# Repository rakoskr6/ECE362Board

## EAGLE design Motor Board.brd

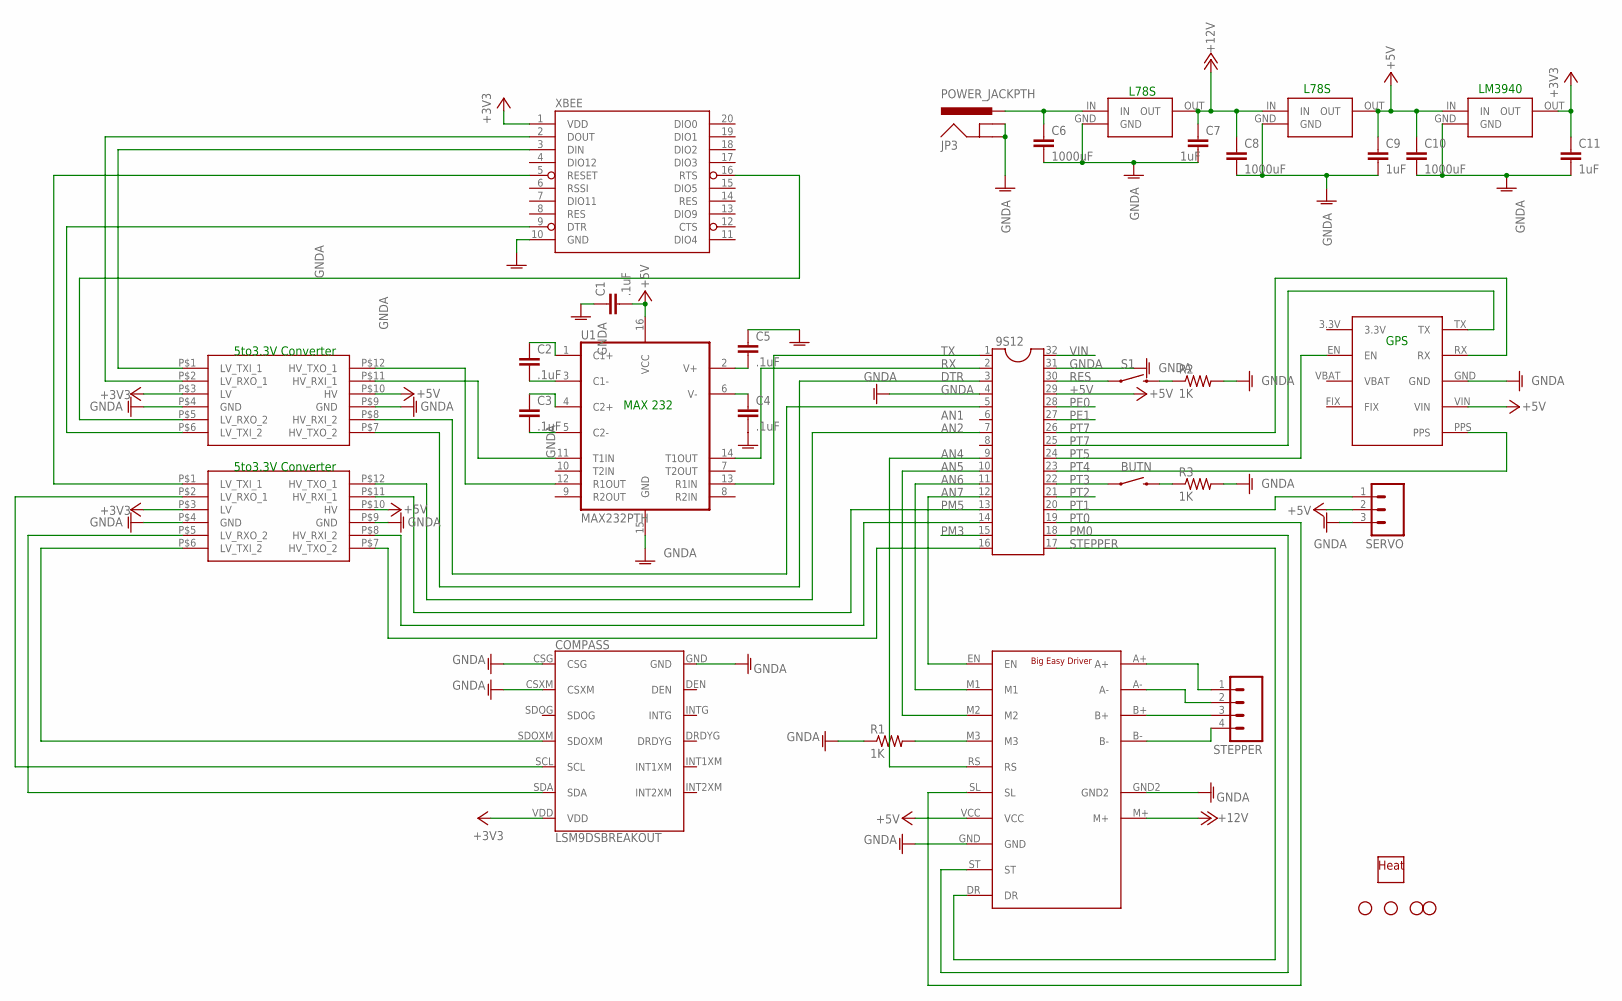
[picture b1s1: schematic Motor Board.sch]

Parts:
9S12: DIL32
BUTN: EXTERNALBUTTON
C1, C2, C3, C4, C5: .1uF; CAP-PTH-SMALL
C6, C8, C10: 1000uF; CAP
C7, C9, C11: 1uF; CAP-PTH-SMALL
COMPASS: LSM9DSBREAKOUT; IMUBREAKOUT
JP3: POWER_JACKPTH; POWER_JACK_PTH
R1, R2, R3: 1K; AXIAL-0.4
REG_5TO3.3: POWERREG_5TO3.3_NOHEAT; POWERREG_NOHEAT
REG_12TO5: POWERREG_12TO5; POWERREG
REG_18TO12: POWERREG18VTO12V; POWERREG
S1: SWITCH-MOMENTARY-2PTH; TACTILE-PTH
SERVO: M03PTH; 1X03
STANDOFF1, STANDOFF2, STANDOFF3, STANDOFF4: STAND-OFF
STEPPER: M04NO_SILK_ALL_ROUND; 1X04_NO_SILK_ALL_ROUND
U1: MAX232PTH; DIL16
U$1, U$2: 5to3.3; LOGIC_LEVEL_CONVERTER
U$3: BIGEASYDRIVER
U$4: GPS
U$9: HEATSINK
XBEE: XBEE-1B1; XBEE-1

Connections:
+3V3: C11.1, COMPASS.VDD, REG_5TO3.3.OUT, U$1.P$3 (LV), U$2.P$3 (LV), XBEE.1 (VDD)
+5V: 9S12.29, C1.2, C9.1, C10.1, REG_5TO3.3.IN, REG_12TO5.OUT, SERVO.2, U1.16 (VCC), U$1.P$10 (HV), U$2.P$10 (HV), U$3.VCC, U$4.VIN
+12V: C7.1, C8.1, REG_12TO5.IN, REG_18TO12.OUT, U$3.M+
A+: STEPPER.1, U$3.A+
A-: STEPPER.2, U$3.A-
AN0: U$2.P$5 (LV_RXO_2), XBEE.16 (RTS)
AN1: U$2.P$6 (LV_TXI_2), XBEE.9 (DTR)
AN2: U$1.P$1 (LV_TXI_1), XBEE.5 (RESET)
AN4: 9S12.9, U$3.RS
AN5: 9S12.10, U$3.M2
AN6: 9S12.11, U$3.M1
AN7: 9S12.12, U$3.EN
B-: STEPPER.4, U$3.B-
DTR: 9S12.3, U$2.P$7 (HV_TXO_2)
GNDA: 9S12.4, 9S12.31, C1.1, C4.2, C5.1, C6.2, C7.2, C8.2, C9.2, C10.2, C11.2, COMPASS.CSG, COMPASS.CSXM, COMPASS.GND, JP3.GND, JP3.GNDBREAK, R1.P$1 (1), R2.P$2 (2), R3.P$2 (2), REG_5TO3.3.GND, REG_12TO5.GND, REG_18TO12.GND, SERVO.3, U1.15 (GND), U$1.P$4 (GND), U$1.P$9 (GND), U$2.P$4 (GND), U$2.P$9 (GND), U$3.GND, U$3.GND2, U$4.GND, XBEE.10 (GND)
unnamed: COMPASS.SCL, U$1.P$2 (LV_RXO_1)
unnamed: COMPASS.SDA, U$1.P$5 (LV_RXO_2)
unnamed: 9S12.7, U$1.P$12 (HV_TXO_1)
unnamed: R1.P$2 (2), U$3.M3
unnamed: 9S12.1, U1.13 (R1IN)
unnamed: 9S12.25, U$4.TX
unnamed: STEPPER.3, U$3.B+
unnamed: 9S12.2, U1.14 (T1OUT)
unnamed: 9S12.5, U$2.P$8 (HV_RXI_2)
unnamed: U1.12 (R1OUT), U$2.P$12 (HV_TXO_1)
unnamed: U1.11 (T1IN), U$2.P$11 (HV_RXI_1)
unnamed: C2.1, U1.1 (C1+)
unnamed: C2.2, U1.3 (C1-)
unnamed: C3.2, U1.5 (C2-)
unnamed: C3.1, U1.4 (C2+)
unnamed: C5.2, U1.2 (V+)
unnamed: C4.1, U1.6 (V-)
unnamed: R2.P$1 (1), S1.3 (2)
unnamed: C6.1, JP3.PWR, REG_18TO12.IN
unnamed: BUTN.2, R3.P$1 (1)
PE0: 9S12.28
PE1: 9S12.27
PM0: 9S12.18, U$3.ST
PM2: 9S12.16, U$1.P$7 (HV_TXO_2)
PM2_NEW: COMPASS.SDOXM, U$1.P$6 (LV_TXI_2)
PM3: 9S12.15
PM4: 9S12.14, U$1.P$8 (HV_RXI_2)
PM5: 9S12.13, U$1.P$11 (HV_RXI_1)
PT0: 9S12.19, U$3.SL
PT1: 9S12.20, SERVO.1
PT2: 9S12.21
PT3: 9S12.22, BUTN.1
PT4: 9S12.23, U$4.PPS
PT5: 9S12.24, U$4.EN
PT7: 9S12.26, U$4.RX
RES: 9S12.30, S1.1
RX: U$2.P$2 (LV_RXO_1), XBEE.2 (DOUT)
STEPPER: 9S12.17, U$3.DR
TX: U$2.P$1 (LV_TXI_1), XBEE.3 (DIN)
VIN: 9S12.32

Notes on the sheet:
GPS
MAX 232
5to3.3V Converter
L78S
LM3940

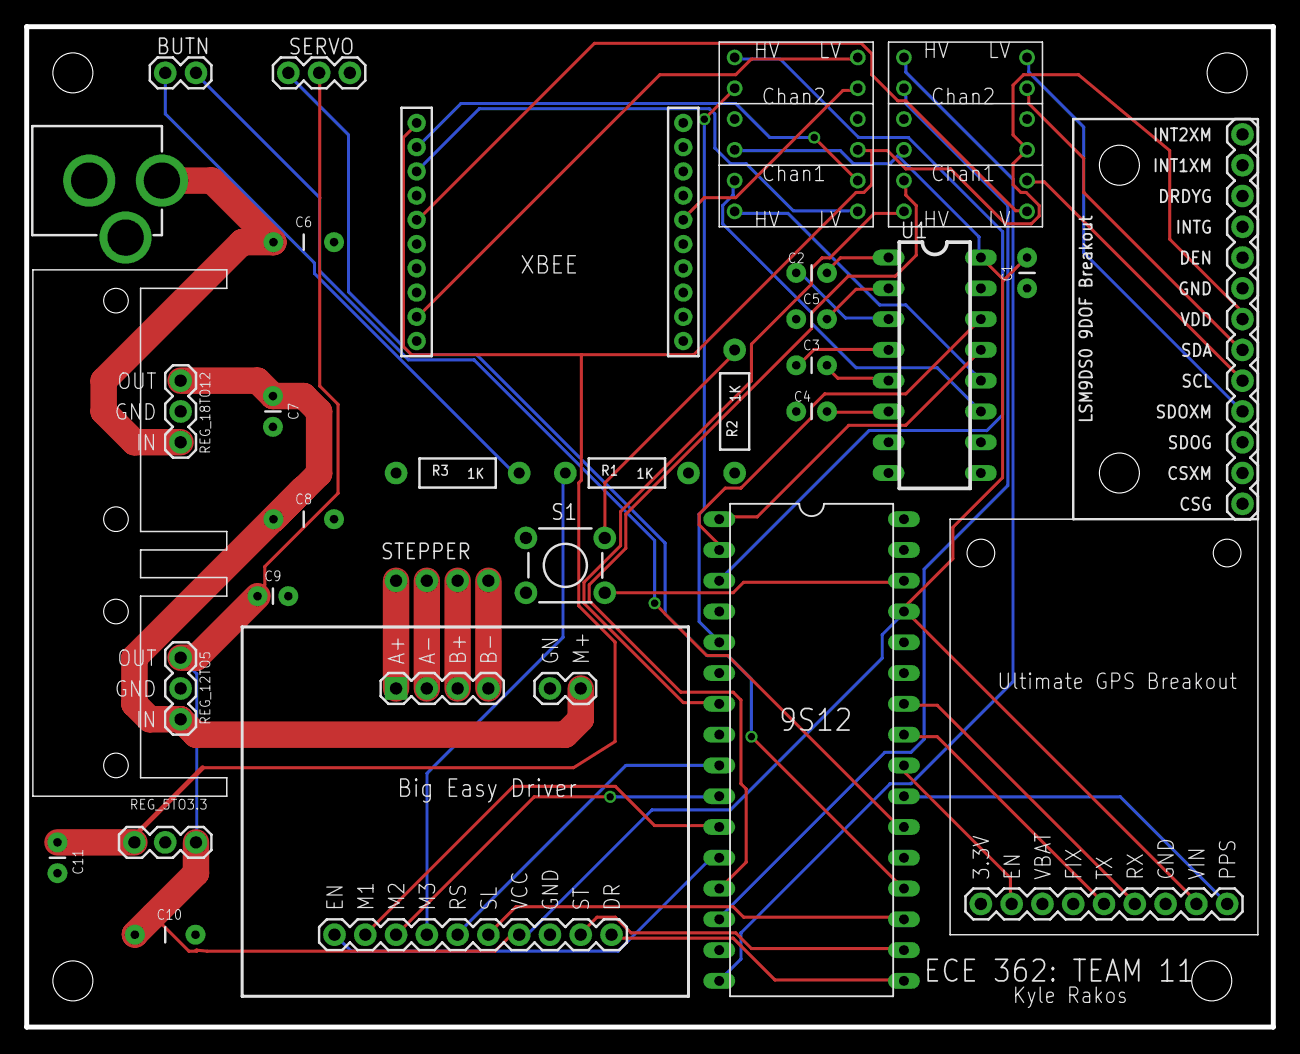
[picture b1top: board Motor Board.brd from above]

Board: 2 copper layers, 102.9 x 82.5 mm, 35 parts (0 on the bottom side), 50 nets.

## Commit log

2015-09-23 :lollipop: Added .gitattributes & .gitignore files

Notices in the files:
parts and their libraries:
SparkFun-RF: Licensing: Creative Commons ShareAlike 4.0 International - https://creativecommons.org/licenses/by-sa/4.0
